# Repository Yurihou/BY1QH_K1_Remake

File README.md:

# BY1QH_K1_Remake
CQ DE BH9DWE! Elecraft is a famous amateur radio manufacturer but its rather expensive to afford. These days I tried to read and understood the original equipment Elecraft K1's principle and managed to modify it. So I push the PCB files to my GitHub and share it to all HAMs.

Firstly I read the manual and understood the schematic diagram of K1, found some components, such as JFET J309, is not available in online shopping network. So I modified the design a little bit. Then I bought and soldered the components of receiver of K1 on the board. After a series of debugging, I managed to make the circuit receiving CW signals on amateur bands. The testing video refers to https://www.bilibili.com/video/BV1d5411i7so

The receiver is succeed in receiving but there is still some problems such as amplifier noise, RF filter attenuation and frequency drift, so I tried to draw the circuit into PCB. If the PCB version works well, I will continue adding functions and modifying design to improve its performance, such as adding frequency display, PLL, multi-band filter and band controller, transmitter, SSB module, antenna tuneing unit and so on.

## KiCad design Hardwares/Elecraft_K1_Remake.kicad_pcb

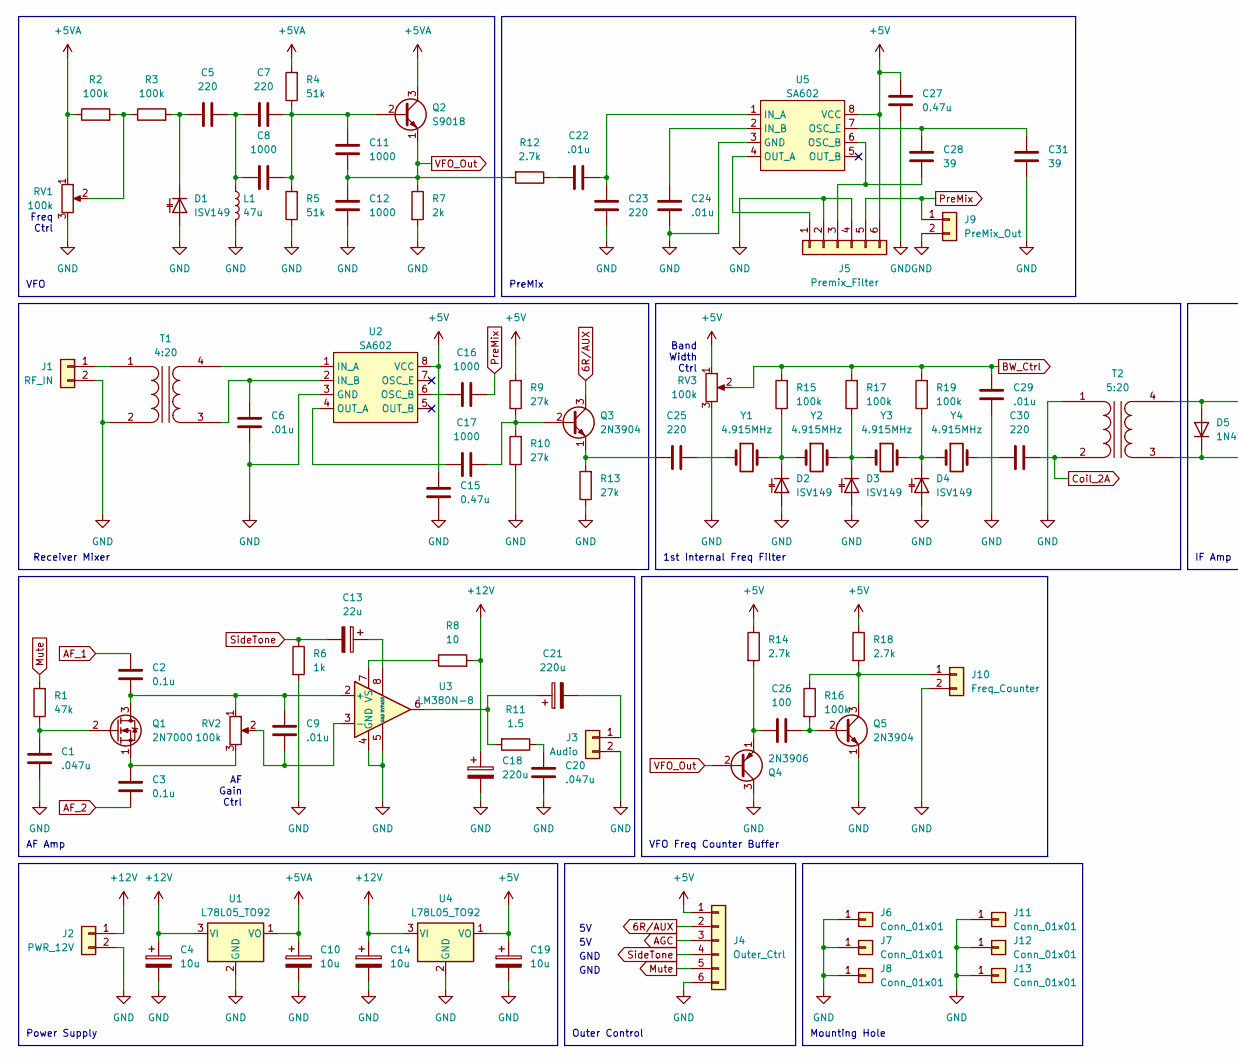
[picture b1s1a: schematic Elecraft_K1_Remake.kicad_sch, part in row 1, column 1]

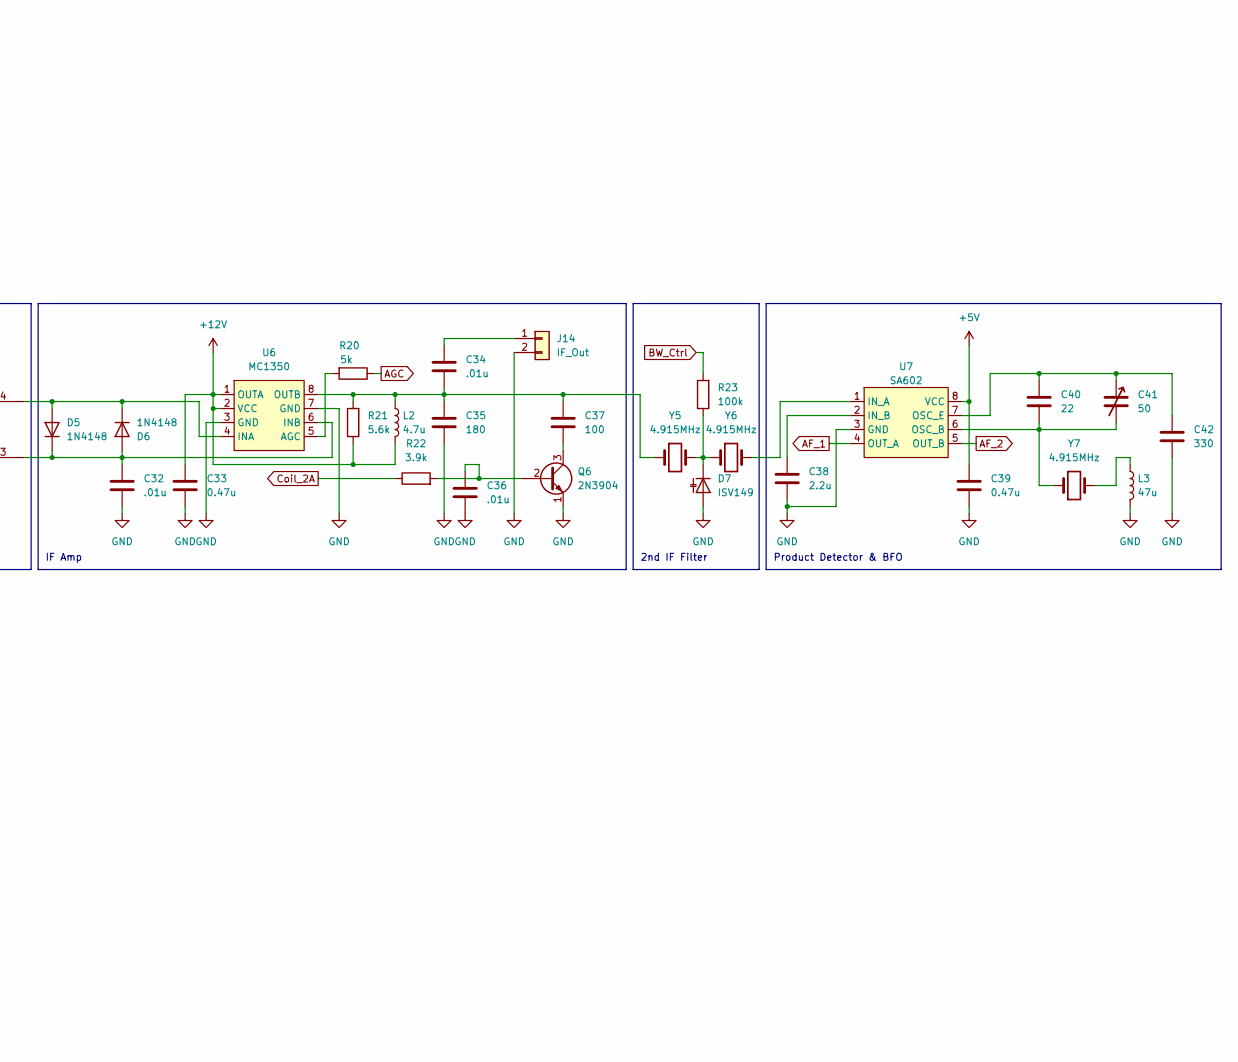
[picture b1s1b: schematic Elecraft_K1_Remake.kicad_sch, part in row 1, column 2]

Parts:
C1, C20: .047u; C_Disc_D5.1mm_W3.2mm_P5.00mm
C2, C3: 0.1u; C_Disc_D5.1mm_W3.2mm_P5.00mm
C4, C10, C14, C19: 10u; CP_Radial_D5.0mm_P2.50mm
C5, C7, C23, C25, C30: 220; C_Disc_D5.1mm_W3.2mm_P5.00mm
C6, C9, C22, C24, C29, C32, C34, C36: .01u; C_Disc_D5.1mm_W3.2mm_P5.00mm
C8, C11, C12, C16, C17: 1000; C_Disc_D5.1mm_W3.2mm_P5.00mm
C13: 22u; CP_Radial_D8.0mm_P2.50mm
C15, C27, C33, C39: 0.47u; C_Disc_D5.1mm_W3.2mm_P5.00mm
C18, C21: 220u; CP_Radial_D8.0mm_P2.50mm
C26, C37: 100; C_Disc_D5.1mm_W3.2mm_P5.00mm
C28, C31: 39; C_Disc_D5.1mm_W3.2mm_P5.00mm
C35: 180; C_Disc_D5.1mm_W3.2mm_P5.00mm
C38: 2.2u; CP_Radial_D5.0mm_P2.50mm
C40: 22; C_Disc_D5.1mm_W3.2mm_P5.00mm
C41: 50; CP_Radial_Tantal_D6.0mm_P5.00mm
C42: 330; C_Disc_D5.1mm_W3.2mm_P5.00mm
D1, D2, D3, D4, D7: ISV149; TO-92-2
D5, D6: 1N4148; D_DO-35_SOD27_P7.62mm_Horizontal
J1: RF_IN; JST_XH_S2B-XH-A_1x02_P2.50mm_Horizontal
J2: PWR_12V; JST_XH_S2B-XH-A_1x02_P2.50mm_Horizontal
J3: Audio; JST_XH_S2B-XH-A_1x02_P2.50mm_Horizontal
J4: Outer_Ctrl; PinSocket_1x06_P2.54mm_Vertical
J5: Premix_Filter; PinSocket_1x06_P2.54mm_Vertical
J6, J7, J8, J11, J12, J13: Conn_01x01; MountingHole_3.2mm_M3_ISO14580_Pad
J9: PreMix_Out; JST_XH_S2B-XH-A_1x02_P2.50mm_Horizontal
J10: Freq_Counter; JST_XH_S2B-XH-A_1x02_P2.50mm_Horizontal
J14: IF_Out; JST_XH_S2B-XH-A_1x02_P2.50mm_Horizontal
L1, L3: 47u; L_Axial_L7.0mm_D3.3mm_P12.70mm_Horizontal_Fastron_MICC
L2: 4.7u; L_Axial_L7.0mm_D3.3mm_P12.70mm_Horizontal_Fastron_MICC
Q1: 2N7000; TO-92_Inline
Q2: S9018; TO-92_Inline
Q3, Q5, Q6: 2N3904; TO-92_Inline
Q4: 2N3906; TO-92_Inline
R1: 47k; R_Axial_DIN0207_L6.3mm_D2.5mm_P7.62mm_Horizontal
R2, R3, R15, R16, R17, R19, R23: 100k; R_Axial_DIN0207_L6.3mm_D2.5mm_P7.62mm_Horizontal
R4, R5: 51k; R_Axial_DIN0207_L6.3mm_D2.5mm_P7.62mm_Horizontal
R6: 1k; R_Axial_DIN0207_L6.3mm_D2.5mm_P7.62mm_Horizontal
R7: 2k; R_Axial_DIN0207_L6.3mm_D2.5mm_P7.62mm_Horizontal
R8: 10; R_Axial_DIN0207_L6.3mm_D2.5mm_P7.62mm_Horizontal
R9, R10, R13: 27k; R_Axial_DIN0207_L6.3mm_D2.5mm_P7.62mm_Horizontal
R11: 1.5; R_Axial_DIN0207_L6.3mm_D2.5mm_P7.62mm_Horizontal
R12, R14, R18: 2.7k; R_Axial_DIN0207_L6.3mm_D2.5mm_P7.62mm_Horizontal
R20: 5k; R_Axial_DIN0207_L6.3mm_D2.5mm_P7.62mm_Horizontal
R21: 5.6k; R_Axial_DIN0207_L6.3mm_D2.5mm_P7.62mm_Horizontal
R22: 3.9k; R_Axial_DIN0207_L6.3mm_D2.5mm_P7.62mm_Horizontal
RV1, RV2, RV3: 100k; JST_XH_S3B-XH-A_1x03_P2.50mm_Horizontal
T1: 4:20; Transformer_Toroid_Horizontal_D12.5mm_Amidon-T44
T2: 5:20; Transformer_Toroid_Horizontal_D12.5mm_Amidon-T44
U1, U4: L78L05_TO92; TO-92_Inline
U2, U5, U7: SA602; DIP-8_W7.62mm_Socket
U3: LM380N-8; DIP-8_W7.62mm_Socket
U6: MC1350; DIP-8_W7.62mm_Socket
Y1, Y2, Y3, Y4, Y5, Y6, Y7: 4.915MHz; Crystal_HC49-U_Vertical

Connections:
6R/AUX: J4.2, Q3.3 (C)
+5V: C15.2, C19.1, C27.2, C39.2, J4.1, J5.6, R9.2, R14.1, R18.1, RV3.1, U2.8 (VCC), U4.1 (VO), U5.8 (VCC), U7.8 (VCC)
+5VA: C10.1, Q2.3 (C), R2.1, R4.2, RV1.1, U1.1 (VO)
+12V: C4.1, C14.1, C18.1, C33.2, J2.1, L2.2, R8.2, R21.1, U1.3 (VI), U4.3 (VI), U6.1 (OUTA), U6.2 (VCC)
AF_1: C2.1, U7.4 (OUT_A)
AF_2: C3.1, U7.5 (OUT_B)
AGC: J4.3, R20.1
BW_Ctrl: C29.1, R15.2, R17.2, R19.2, R23.2, RV3.2
Coil_2A: C30.2, R22.1, T2.2 (AB)
GND: C1.2, C4.2, C6.2, C10.2, C12.2, C14.2, C15.1, C18.2, C19.2, C20.2, C23.1, C24.2, C27.1, C29.2, C31.2, C32.2, C33.1, C35.1, C36.2, C38.2, C39.1, C42.2, D1.2 (A), D2.2 (A), D3.2 (A), D4.2 (A), D7.2 (A), J1.2, J2.2, J3.2, J4.6, J5.2, J5.4, J6.1, J7.1, J8.1, J9.2, J10.2, J11.1, J12.1, J13.1, J14.2, L1.2, L3.2, Q4.3 (C), Q5.1 (E), Q6.1 (E), R5.1, R6.2, R7.2, R10.1, R13.1, RV1.3, RV3.3, T1.2 (AB), T2.1 (AA), U1.2 (GND), U2.3 (GND), U3.4 (GND), U3.5 (GND), U4.2 (GND), U5.3 (GND), U6.3 (GND), U6.7 (GND), U7.3 (GND)
Mute: J4.5, R1.2
unnamed: C5.1, C7.2, C8.2, L1.1
unnamed: C20.1, R11.1
unnamed: C21.1, R11.2, U3.6
unnamed: C22.2, R12.1
unnamed: C25.2, Y1.1
unnamed: C30.1, Y4.2
unnamed: C5.2, D1.1 (K), R3.2
unnamed: D2.1 (K), R15.1, Y1.2, Y2.1
unnamed: D3.1 (K), R17.1, Y2.2, Y3.1
unnamed: D4.1 (K), R19.1, Y3.2, Y4.1
unnamed: D5.2 (A), D6.1 (K), T2.4 (SB), U6.4 (INA)
unnamed: C32.1, D5.1 (K), D6.2 (A), T2.3 (SA), U6.6 (INB)
unnamed: D7.1 (K), R23.1, Y5.2, Y6.1
unnamed: J1.1, T1.1 (AA)
unnamed: C21.2, J3.1
unnamed: J5.1, U5.4 (OUT_A)
unnamed: C28.2, J5.3, U5.6 (OSC_B)
unnamed: J10.1, Q5.3 (C), R16.1, R18.2
unnamed: C34.1, J14.1
unnamed: L3.1, Y7.2
unnamed: C2.2, C9.1, Q1.3 (D), RV2.1, U3.2 (+)
unnamed: C1.1, Q1.2 (G), R1.1
unnamed: C3.2, Q1.1 (S), RV2.3
unnamed: C7.1, C8.1, C11.1, Q2.2 (B), R4.1, R5.2
unnamed: C17.2, Q3.2 (B), R9.1, R10.2
unnamed: C25.1, Q3.1 (E), R13.2
unnamed: C26.2, Q4.1 (E), R14.2
unnamed: C26.1, Q5.2 (B), R16.2
unnamed: C36.1, Q6.2 (B), R22.2
unnamed: C37.1, Q6.3 (C)
unnamed: R2.2, R3.1, RV1.2
unnamed: C6.1, T1.3 (SA), U2.2 (IN_B)
unnamed: T1.4 (SB), U2.1 (IN_A)
unnamed: C16.1, U2.6 (OSC_B)
unnamed: C17.1, U2.4 (OUT_A)
unnamed: C9.2, RV2.2, U3.3 (-)
unnamed: C13.1, U3.8 (BYPASS)
unnamed: R8.1, U3.7 (VS)
unnamed: C22.1, C23.2, U5.1 (IN_A)
unnamed: C24.1, U5.2 (IN_B)
unnamed: C28.1, C31.1, U5.7 (OSC_E)
unnamed: R20.2, U6.5 (AGC)
unnamed: C34.2, C35.2, C37.2, L2.1, R21.2, U6.8 (OUTB), Y5.1
unnamed: U7.1 (IN_A), Y6.2
unnamed: C38.1, U7.2 (IN_B)
unnamed: C40.2, C41.2, U7.6 (OSC_B), Y7.1
unnamed: C40.1, C41.1, C42.1, U7.7 (OSC_E)
PreMix: C16.2, J5.5, J9.1
SideTone: C13.2, J4.4, R6.1
VFO_Out: C11.2, C12.1, Q2.1 (E), Q4.2 (B), R7.1, R12.2

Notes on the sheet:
2nd IF Filter
Band Width Ctrl
VFO Freq Counter Buffer
Power Supply
GND
Freq Ctrl
PreMix
Mounting Hole
Outer Control
VFO
Product Detector & BFO
AF Gain Ctrl
AF Amp
Receiver Mixer
1st Internal Freq Filter
IF Amp

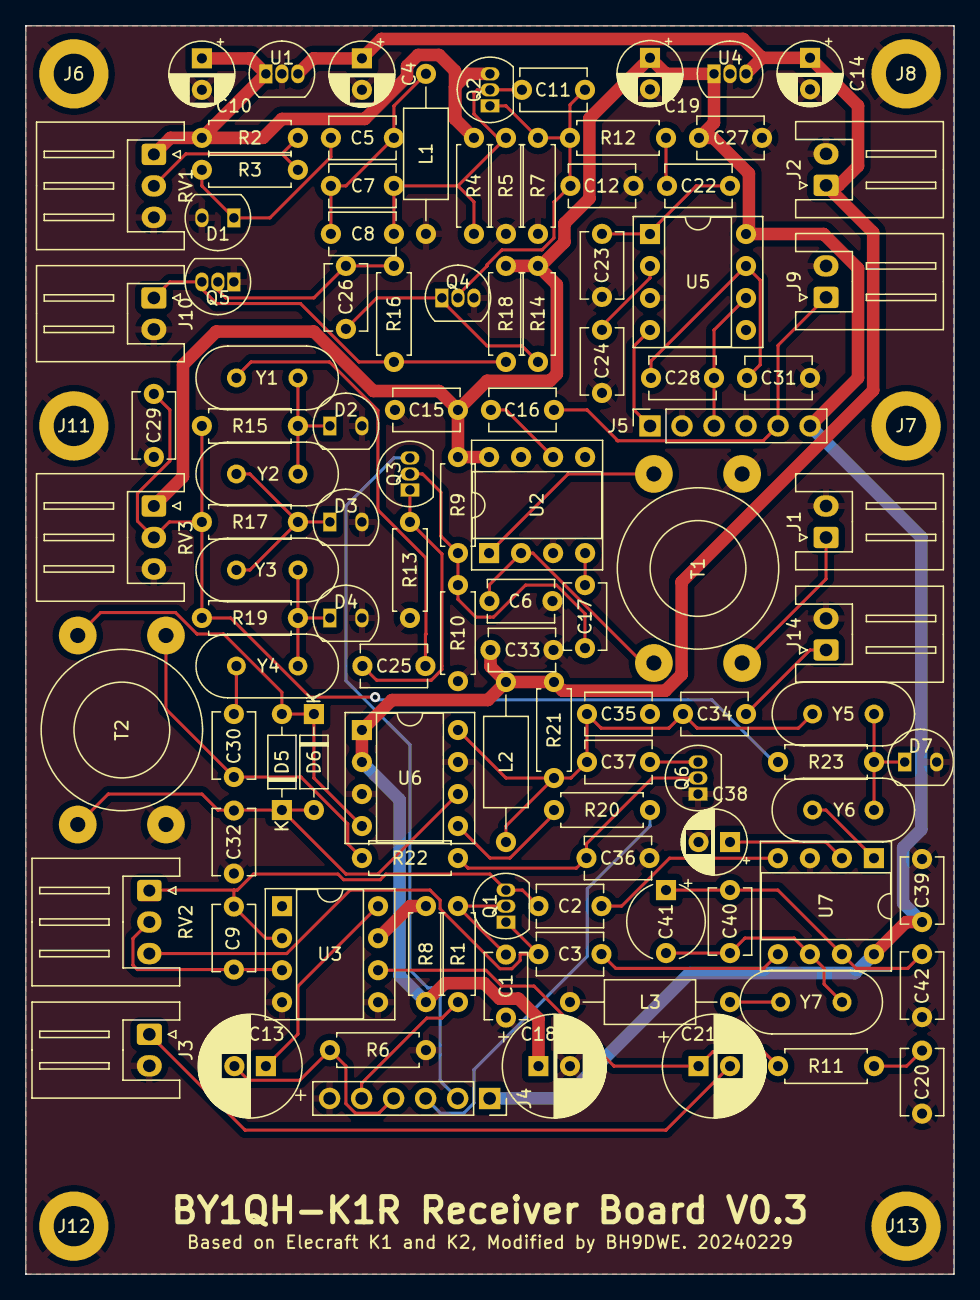
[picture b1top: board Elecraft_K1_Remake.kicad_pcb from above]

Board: 2 copper layers, 73.7 x 99.1 mm, 114 parts (0 on the bottom side), 61 nets.

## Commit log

2024-01-15 Add hardware PCB files
2024-01-15 Create Hardwares
2024-01-15 Rename Elecraft_K1_Remake.kicad_prl to Hardwares/Elecraft_K1_Remake.kicad_prl
2024-01-15 Rename Elecraft_K1_Remake.kicad_pro to Hardwares/Elecraft_K1_Remake.kicad_pro
2024-01-15 Rename fp-info-cache to Hardwares/fp-info-cache
